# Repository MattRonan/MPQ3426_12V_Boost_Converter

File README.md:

# MPQ3426_Boost_Converter

I made this 3.7V to 12V boost board to be able to power little solenoids from lipo packs.  All caps should be greater than 12V, diode should be at least 3A, and the inductor should have an Isat value of at least 5A.

Made with Eagle 9.6

Osh Park link: https://oshpark.com/shared_projects/3ssml9ry

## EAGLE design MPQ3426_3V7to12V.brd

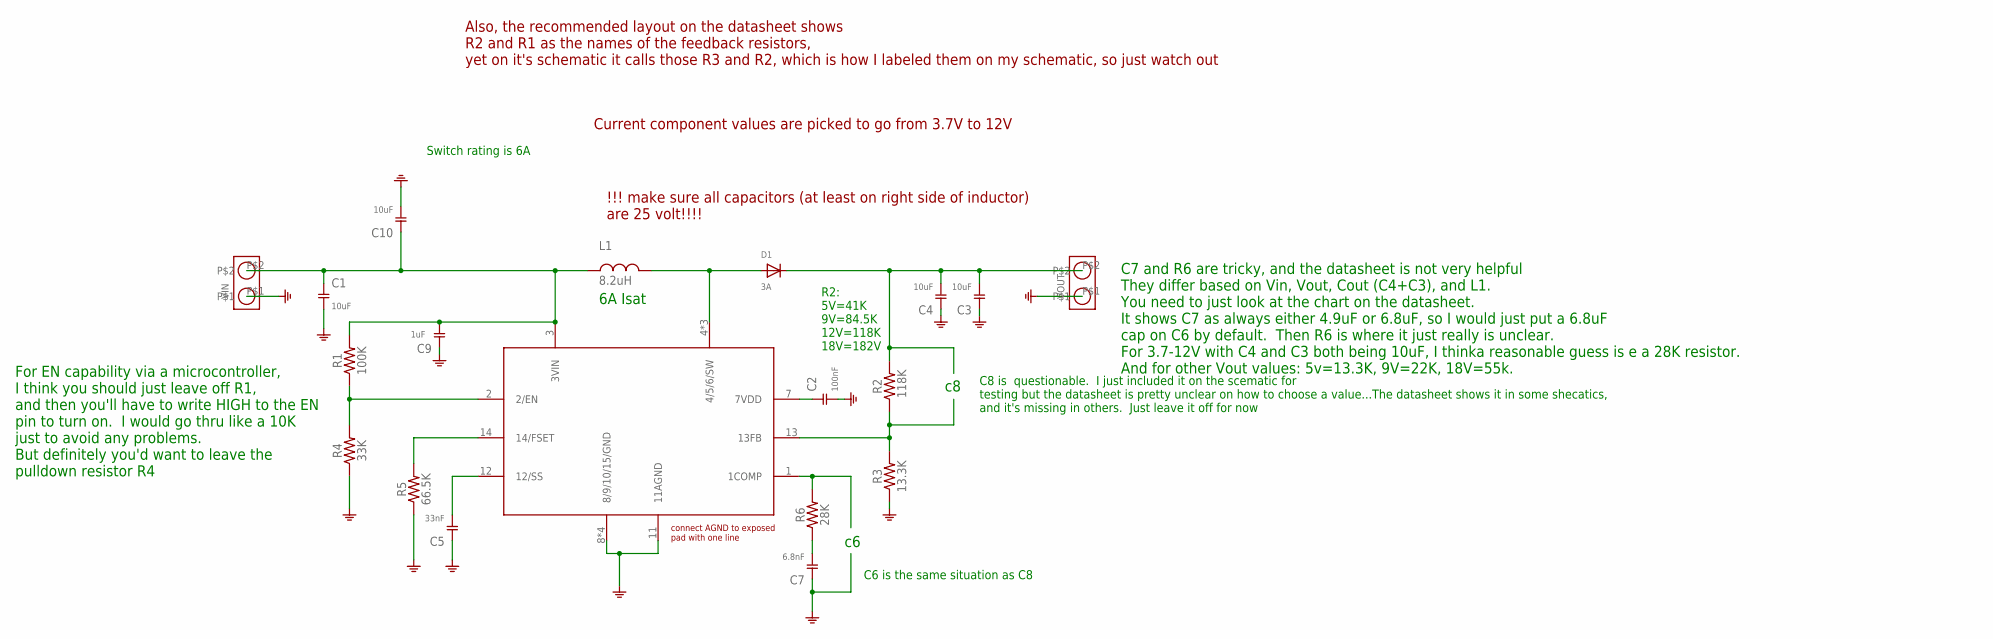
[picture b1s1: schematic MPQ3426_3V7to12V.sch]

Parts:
C1, C3, C4, C10: 10uF; 0805-NORMAL
C2: 100nF; 0603_NORMAL
C5: 33nF; 0603_NORMAL
C7: 6.8nF; 0603_NORMAL
C9: 1uF; 0603_NORMAL
D1: 3A; SOD-123FL
L1: 8.2uH; INDUCTOR_UNIVERSAL_LARGE
R1: 100K; 0603_NORMAL
R2: 118K; 0603_NORMAL
R3: 13.3K; 0603_NORMAL
R4: 33K; 0603_NORMAL
R5: 66.5K; 0603_NORMAL
R6: 28K; 0603_NORMAL
U$1: MPQ3426
VIN: HEADER_1X2_SQUARE_SMD; 1X2_.1"_2.54_SMD
VOUT: HEADER_1X2_SQUARE_SMD; 1X2_.1"_2.54_SMD

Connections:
GND: C1.2, C2.2, C3.1, C4.1, C5.1, C7.1, C9.1, C10.2, R3.1, R4.1, R5.1, U$1.8 (8/9/10/15/GND), U$1.9 (8/9/10/15/GND), U$1.10 (8/9/10/15/GND), U$1.11 (11AGND), U$1.P$1 (8/9/10/15/GND), VIN.P$1, VOUT.P$1
unnamed: D1.A, L1.P$2 (2), U$1.4 (4/5/6/SW), U$1.5 (4/5/6/SW), U$1.6 (4/5/6/SW)
unnamed: R1.1, R4.2, U$1.2 (2/EN)
unnamed: R5.2, U$1.14 (14/FSET)
unnamed: C5.2, U$1.12 (12/SS)
unnamed: C2.1, U$1.7 (7VDD)
unnamed: R2.1, R3.2, U$1.13 (13FB)
unnamed: R6.2, U$1.1 (1COMP)
unnamed: C7.2, R6.1
VIN: C1.1, C9.2, C10.1, L1.P$1 (1), R1.2, U$1.3 (3VIN), VIN.P$2
VOUT: C3.2, C4.2, D1.C, R2.2, VOUT.P$2

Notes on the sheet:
Switch rating is 6A
C8 is questionable. I just included it on the scematic for testing but the datasheet is pretty unclear on how to choose a value...The datasheet shows it in some shecatics, and it's missing in others. Just leave it off for now
C6 is the same situation as C8
R2: 5V=41K 9V=84.5K 12V=118K 18V=182V
!!! make sure all capacitors (at least on right side of inductor) are 25 volt!!!!
6A Isat
C7 and R6 are tricky, and the datasheet is not very helpful They differ based on Vin, Vout, Cout (C4+C3), and L1. You need to just look at the chart on the datasheet. It shows C7 as always either 4.9uF or 6.8uF, so I would just put a 6.8uF cap on C6 by default. Then R6 is where it just really is un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
Current component values are picked to go from 3.7V to 12V
Also, the recommended layout on the datasheet shows R2 and R1 as the names of the feedback resistors, yet on it's schematic it calls those R3 and R2, which is how I labeled them on my schematic, so just watch out
For EN capability via a microcontroller, I think you should just leave off R1, and then you'll have to write HIGH to the EN pin to turn on. I would go thru like a 10K just to avoid any problems. But definitely you'd want to leave the pulldown resistor R4

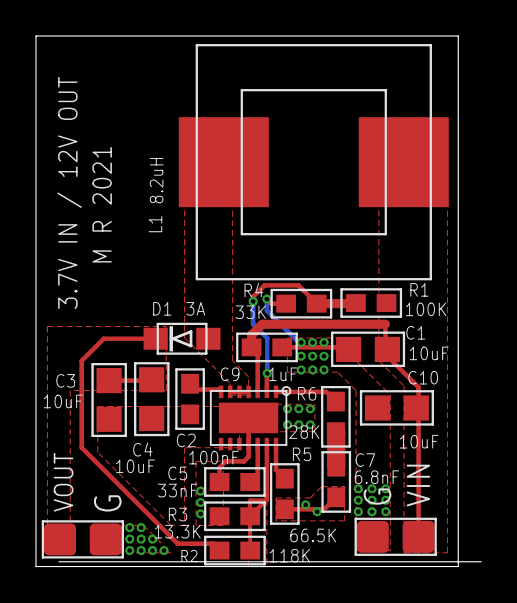
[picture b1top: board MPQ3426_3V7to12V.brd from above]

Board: 2 copper layers, 24.7 x 29.5 mm, 19 parts (0 on the bottom side), 11 nets.

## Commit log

2022-08-10 Create BOM
